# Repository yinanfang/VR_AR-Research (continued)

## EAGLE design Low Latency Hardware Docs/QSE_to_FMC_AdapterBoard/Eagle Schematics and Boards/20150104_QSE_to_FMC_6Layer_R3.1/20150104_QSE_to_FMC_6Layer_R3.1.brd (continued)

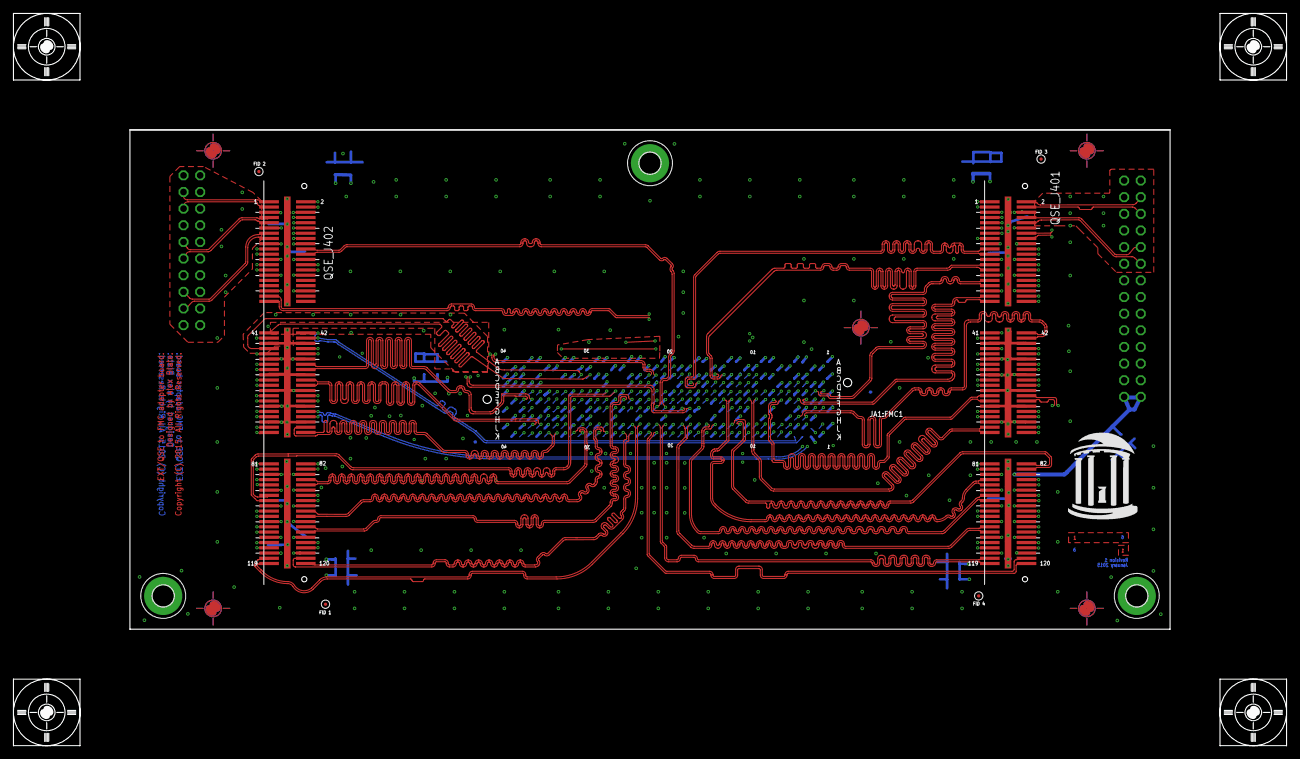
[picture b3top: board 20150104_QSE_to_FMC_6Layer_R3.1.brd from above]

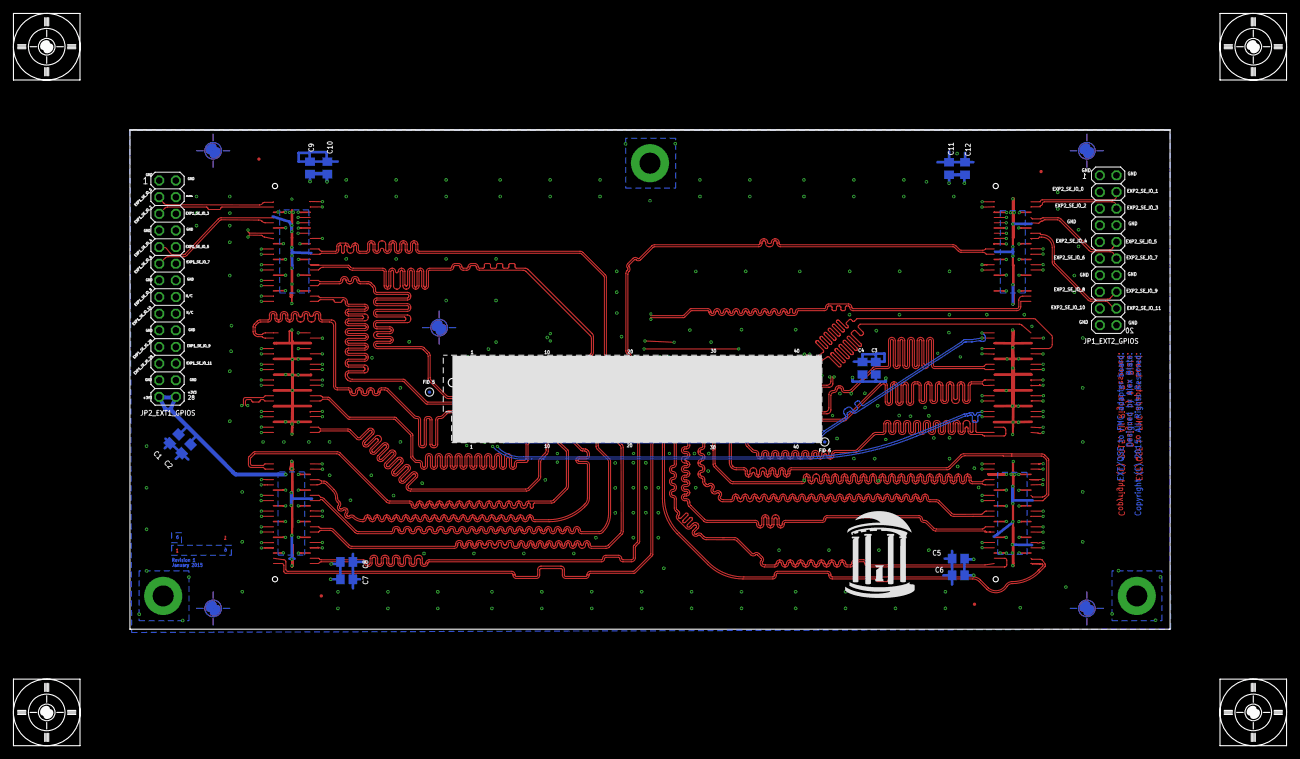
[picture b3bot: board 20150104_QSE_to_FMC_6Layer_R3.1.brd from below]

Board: 6 copper layers, 158.8 x 76.2 mm, 30 parts (15 on the bottom side), 165 nets.

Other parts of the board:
DRILEGEND: DRILEGEND
JA1:FMC1: >NAME; ASP-134486-01
QSE_J401, QSE_J402: QSE-060-01
U$2, U$3, U$4, U$5, U$6: PASS-ROUND
U$8, U$9, U$10, U$11: ALIGNMENT

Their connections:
+2V5: QSE_J401.5, QSE_J401.6, QSE_J401.11, QSE_J401.12, QSE_J401.17, QSE_J401.18, QSE_J401.23, QSE_J401.24, QSE_J401.29, QSE_J401.30, QSE_J401.35, QSE_J401.36, QSE_J402.5, QSE_J402.6, QSE_J402.11, QSE_J402.12, QSE_J402.17, QSE_J402.18, QSE_J402.23, QSE_J402.24, QSE_J402.29, QSE_J402.30, QSE_J402.35, QSE_J402.36; also elsewhere on the board
+3V3: JA1:FMC1.C39, JA1:FMC1.D36, JA1:FMC1.D38, JA1:FMC1.D40, QSE_J401.85, QSE_J401.86, QSE_J401.91, QSE_J401.92, QSE_J401.97, QSE_J401.98, QSE_J401.103, QSE_J401.104, QSE_J401.109, QSE_J401.110, QSE_J401.115, QSE_J401.116, QSE_J402.85, QSE_J402.86, QSE_J402.91, QSE_J402.92, QSE_J402.97, QSE_J402.98, QSE_J402.103, QSE_J402.104, QSE_J402.109, QSE_J402.110, QSE_J402.115, QSE_J402.116; also elsewhere on the board
CLK0_M2C_N: JA1:FMC1.H5, QSE_J401.44
CLK0_M2C_P: JA1:FMC1.H4, QSE_J401.42
CLK1_M2C_N: JA1:FMC1.G3, QSE_J401.74
CLK1_M2C_P: JA1:FMC1.G2, QSE_J401.72
CLK2_M2C_N: JA1:FMC1.K5, QSE_J402.44
CLK2_M2C_P: JA1:FMC1.K4, QSE_J402.42
CLK3_M2C_N: JA1:FMC1.J3, QSE_J402.74
CLK3_M2C_P: JA1:FMC1.J2, QSE_J402.72
EXP1_SE_CLK_IN: JA1:FMC1.H35, QSE_J401.43
EXP1_SE_CLK_OUT: JA1:FMC1.G34, QSE_J401.49
EXP1_SE_IO_0: QSE_J401.2; also elsewhere on the board
EXP1_SE_IO_1: QSE_J401.1; also elsewhere on the board
EXP1_SE_IO_2: QSE_J401.4; also elsewhere on the board
EXP1_SE_IO_3: QSE_J401.3; also elsewhere on the board
EXP1_SE_IO_4: QSE_J401.8; also elsewhere on the board
EXP1_SE_IO_5: QSE_J401.7; also elsewhere on the board
EXP1_SE_IO_6: QSE_J401.10; also elsewhere on the board
EXP1_SE_IO_7: QSE_J401.9; also elsewhere on the board
EXP1_SE_IO_8: QSE_J401.14; also elsewhere on the board
EXP1_SE_IO_9: QSE_J401.13; also elsewhere on the board
EXP1_SE_IO_10: QSE_J401.16; also elsewhere on the board
EXP1_SE_IO_11: QSE_J401.15; also elsewhere on the board
EXP1_SE_IO_28: QSE_J401.41; also elsewhere on the board
EXP1_SE_IO_29: QSE_J401.47; also elsewhere on the board
EXP2_SE_CLK_IN: JA1:FMC1.G37, QSE_J402.43
EXP2_SE_CLK_OUT: JA1:FMC1.H38, QSE_J402.49
EXP2_SE_IO_0: QSE_J402.2; also elsewhere on the board
EXP2_SE_IO_1: QSE_J402.1; also elsewhere on the board
EXP2_SE_IO_2: QSE_J402.4; also elsewhere on the board
EXP2_SE_IO_3: QSE_J402.3; also elsewhere on the board
EXP2_SE_IO_4: QSE_J402.8; also elsewhere on the board
EXP2_SE_IO_5: QSE_J402.7; also elsewhere on the board
EXP2_SE_IO_6: QSE_J402.10; also elsewhere on the board
EXP2_SE_IO_7: QSE_J402.9; also elsewhere on the board
EXP2_SE_IO_8: QSE_J402.14; also elsewhere on the board
EXP2_SE_IO_9: QSE_J402.13; also elsewhere on the board
EXP2_SE_IO_10: QSE_J402.16; also elsewhere on the board
EXP2_SE_IO_11: QSE_J402.15; also elsewhere on the board
FMC_SCL: JA1:FMC1.C30, QSE_J402.41
FMC_SDA: JA1:FMC1.C31, QSE_J402.47
GBCTCLK1_N: JA1:FMC1.B21, QSE_J401.50
GBCTCLK1_P: JA1:FMC1.B20, QSE_J401.48
GBTCLK0_N: JA1:FMC1.D5, QSE_J401.61
GBTCLK0_P: JA1:FMC1.D4, QSE_J401.59
GND: JA1:FMC1.A1, JA1:FMC1.A4, JA1:FMC1.A5, JA1:FMC1.A8, JA1:FMC1.A9, JA1:FMC1.A12, JA1:FMC1.A13, JA1:FMC1.A16, JA1:FMC1.A17, JA1:FMC1.A20, JA1:FMC1.A21, JA1:FMC1.A24, JA1:FMC1.A25, JA1:FMC1.A28, JA1:FMC1.A29, JA1:FMC1.A32, JA1:FMC1.A33, JA1:FMC1.A36, JA1:FMC1.A37, JA1:FMC1.A40, JA1:FMC1.B2, JA1:FMC1.B3, JA1:FMC1.B6, JA1:FMC1.B7, JA1:FMC1.B10, JA1:FMC1.B11, JA1:FMC1.B14, JA1:FMC1.B15, JA1:FMC1.B18, JA1:FMC1.B19, JA1:FMC1.B22, JA1:FMC1.B23, JA1:FMC1.B26, JA1:FMC1.B27, JA1:FMC1.B30, JA1:FMC1.B31, JA1:FMC1.B34, JA1:FMC1.B35, JA1:FMC1.B38, JA1:FMC1.B39, JA1:FMC1.C1, JA1:FMC1.C4, JA1:FMC1.C5, JA1:FMC1.C8, JA1:FMC1.C9, JA1:FMC1.C12, JA1:FMC1.C13, JA1:FMC1.C16, JA1:FMC1.C17, JA1:FMC1.C20, JA1:FMC1.C21, JA1:FMC1.C24, JA1:FMC1.C25, JA1:FMC1.C28, JA1:FMC1.C29, JA1:FMC1.C32, JA1:FMC1.C33, JA1:FMC1.C36, JA1:FMC1.C38, JA1:FMC1.C40, JA1:FMC1.D2, JA1:FMC1.D3, JA1:FMC1.D6, JA1:FMC1.D7, JA1:FMC1.D10, JA1:FMC1.D13, JA1:FMC1.D16, JA1:FMC1.D19, JA1:FMC1.D22, JA1:FMC1.D25, JA1:FMC1.D28, JA1:FMC1.D37, JA1:FMC1.D39, JA1:FMC1.E1, JA1:FMC1.E4, JA1:FMC1.E5, JA1:FMC1.E8, JA1:FMC1.E11, JA1:FMC1.E14, JA1:FMC1.E17, JA1:FMC1.E20, JA1:FMC1.E23, JA1:FMC1.E26, JA1:FMC1.E29, JA1:FMC1.E32, JA1:FMC1.E35, JA1:FMC1.E38, JA1:FMC1.E40, JA1:FMC1.F2, JA1:FMC1.F3, JA1:FMC1.F6, JA1:FMC1.F9, JA1:FMC1.F12, JA1:FMC1.F15, JA1:FMC1.F18, JA1:FMC1.F21, JA1:FMC1.F24, JA1:FMC1.F27, JA1:FMC1.F30, JA1:FMC1.F33, JA1:FMC1.F36, JA1:FMC1.F39, JA1:FMC1.G1, JA1:FMC1.G4, JA1:FMC1.G5, JA1:FMC1.G8, JA1:FMC1.G11, JA1:FMC1.G14, JA1:FMC1.G17, JA1:FMC1.G20, JA1:FMC1.G23, JA1:FMC1.G26, JA1:FMC1.G29, JA1:FMC1.G30, JA1:FMC1.G32, JA1:FMC1.G33, JA1:FMC1.G35, JA1:FMC1.G36, JA1:FMC1.G38, JA1:FMC1.G40, JA1:FMC1.H3, JA1:FMC1.H6, JA1:FMC1.H9, JA1:FMC1.H12, JA1:FMC1.H15, JA1:FMC1.H18, JA1:FMC1.H21, JA1:FMC1.H24, JA1:FMC1.H27, JA1:FMC1.H30, JA1:FMC1.H31, JA1:FMC1.H33, JA1:FMC1.H34, JA1:FMC1.H36, JA1:FMC1.H37, JA1:FMC1.H39, JA1:FMC1.J1, JA1:FMC1.J4, JA1:FMC1.J5, JA1:FMC1.J8, JA1:FMC1.J11, JA1:FMC1.J14, JA1:FMC1.J17, JA1:FMC1.J20, JA1:FMC1.J23, JA1:FMC1.J26, JA1:FMC1.J29, JA1:FMC1.J32, JA1:FMC1.J35, JA1:FMC1.J38, JA1:FMC1.J40, JA1:FMC1.K2, JA1:FMC1.K3, JA1:FMC1.K6, JA1:FMC1.K9, JA1:FMC1.K12, JA1:FMC1.K15, JA1:FMC1.K18, JA1:FMC1.K21, JA1:FMC1.K24, JA1:FMC1.K27, JA1:FMC1.K30, JA1:FMC1.K33, JA1:FMC1.K36, JA1:FMC1.K39, QSE_J401.45, QSE_J401.46, QSE_J401.51, QSE_J401.52, QSE_J401.57, QSE_J401.58, QSE_J401.63, QSE_J401.64, QSE_J401.69, QSE_J401.70, QSE_J401.75, QSE_J401.76, QSE_J401.GND1, QSE_J401.GND2, QSE_J401.GND3, QSE_J401.GND4, QSE_J401.GND5, QSE_J401.GND6, QSE_J401.GND7, QSE_J401.GND8, QSE_J401.GND9, QSE_J401.GND10, QSE_J401.GND11, QSE_J401.GND12, QSE_J402.45, QSE_J402.46, QSE_J402.51, QSE_J402.52, QSE_J402.57, QSE_J402.58, QSE_J402.63, QSE_J402.64, QSE_J402.69, QSE_J402.70, QSE_J402.75, QSE_J402.76, QSE_J402.GND1, QSE_J402.GND2, QSE_J402.GND3, QSE_J402.GND4, QSE_J402.GND5, QSE_J402.GND6, QSE_J402.GND7, QSE_J402.GND8, QSE_J402.GND9, QSE_J402.GND10, QSE_J402.GND11, QSE_J402.GND12; also elsewhere on the board
HDP0_N: JA1:FMC1.F5, QSE_J401.39
HDP0_P: JA1:FMC1.F4, QSE_J401.37
HDP1_N: JA1:FMC1.E3, QSE_J401.33
HDP1_P: JA1:FMC1.E2, QSE_J401.31
HDP2_N: JA1:FMC1.K8, QSE_J401.55
HDP2_P: JA1:FMC1.K7, QSE_J401.53
HDP3_N: JA1:FMC1.J7, QSE_J401.56
HDP3_P: JA1:FMC1.J6, QSE_J401.54
HDP4_N: JA1:FMC1.F8, QSE_J401.67
HDP4_P: JA1:FMC1.F7, QSE_J401.65
HDP5_N: JA1:FMC1.E7, QSE_J401.62
HDP5_P: JA1:FMC1.E6, QSE_J401.60
HDP6_N: JA1:FMC1.K11, QSE_J401.73
HDP6_P: JA1:FMC1.K10, QSE_J401.71
HDP7_N: JA1:FMC1.J10, QSE_J401.68
HDP7_P: JA1:FMC1.J9, QSE_J401.66
HDP8_N: JA1:FMC1.F11, QSE_J401.79
HDP8_P: JA1:FMC1.F10, QSE_J401.77
HDP9_N: JA1:FMC1.E10, QSE_J401.80
HDP9_P: JA1:FMC1.E9, QSE_J401.78
HDP10_N: JA1:FMC1.K14, QSE_J401.83
HDP10_P: JA1:FMC1.K13, QSE_J401.81
HDP11_N: JA1:FMC1.J13, QSE_J401.84
HDP11_P: JA1:FMC1.J12, QSE_J401.82
HDP12_N: JA1:FMC1.F14, QSE_J401.89
HDP12_P: JA1:FMC1.F13, QSE_J401.87
HDP13_N: JA1:FMC1.E13, QSE_J401.90
HDP13_P: JA1:FMC1.E12, QSE_J401.88
HDP14_N: JA1:FMC1.J16, QSE_J401.95
HDP14_P: JA1:FMC1.J15, QSE_J401.93
HDP15_N: JA1:FMC1.F17, QSE_J401.96
HDP15_P: JA1:FMC1.F16, QSE_J401.94
HDP16_N: JA1:FMC1.E16, QSE_J401.101
HDP16_P: JA1:FMC1.E15, QSE_J401.99
HDP17_N: JA1:FMC1.K17, QSE_J401.102
HDP17_P: JA1:FMC1.K16, QSE_J401.100
HDP18_N: JA1:FMC1.J19, QSE_J401.107
HDP18_P: JA1:FMC1.J18, QSE_J401.105
HDP19_N: JA1:FMC1.F20, QSE_J401.108
HDP19_P: JA1:FMC1.F19, QSE_J401.106
HDP20_N: JA1:FMC1.E19, QSE_J401.113
HDP20_P: JA1:FMC1.E18, QSE_J401.111
HDP21_N: JA1:FMC1.K20, QSE_J401.114
HDP21_P: JA1:FMC1.K19, QSE_J401.112
HDP22_N: JA1:FMC1.J22, QSE_J401.119
HDP22_P: JA1:FMC1.J21, QSE_J401.117
HDP23_N: JA1:FMC1.K23, QSE_J401.120
HDP23_P: JA1:FMC1.K22, QSE_J401.118
HDQ0_N: JA1:FMC1.K26, QSE_J402.120
HDQ0_P: JA1:FMC1.K25, QSE_J402.118
HDQ1_N: JA1:FMC1.J25, QSE_J402.119
HDQ1_P: JA1:FMC1.J24, QSE_J402.117
HDQ2_N: JA1:FMC1.F23, QSE_J402.114
HDQ2_P: JA1:FMC1.F22, QSE_J402.112
HDQ3_N: JA1:FMC1.E22, QSE_J402.113
HDQ3_P: JA1:FMC1.E21, QSE_J402.111
HDQ4_N: JA1:FMC1.F26, QSE_J402.108
HDQ4_P: JA1:FMC1.F25, QSE_J402.106
HDQ5_N: JA1:FMC1.E25, QSE_J402.107
HDQ5_P: JA1:FMC1.E24, QSE_J402.105
HDQ6_N: JA1:FMC1.K29, QSE_J402.102
HDQ6_P: JA1:FMC1.K28, QSE_J402.100
HDQ7_N: JA1:FMC1.J28, QSE_J402.101
HDQ7_P: JA1:FMC1.J27, QSE_J402.99
HDQ8_N: JA1:FMC1.F29, QSE_J402.96
HDQ8_P: JA1:FMC1.F28, QSE_J402.94
HDQ9_N: JA1:FMC1.E28, QSE_J402.95
HDQ9_P: JA1:FMC1.E27, QSE_J402.93
HDQ10_N: JA1:FMC1.K32, QSE_J402.90
HDQ10_P: JA1:FMC1.K31, QSE_J402.88
HDQ11_N: JA1:FMC1.J31, QSE_J402.89
HDQ11_P: JA1:FMC1.J30, QSE_J402.87
HDQ12_N: JA1:FMC1.F32, QSE_J402.84
HDQ12_P: JA1:FMC1.F31, QSE_J402.82
HDQ13_N: JA1:FMC1.E31, QSE_J402.83
HDQ13_P: JA1:FMC1.E30, QSE_J402.81
HDQ14_N: JA1:FMC1.K35, QSE_J402.80
HDQ14_P: JA1:FMC1.K34, QSE_J402.78
HDQ15_N: JA1:FMC1.J34, QSE_J402.79
HDQ15_P: JA1:FMC1.J33, QSE_J402.77
HDQ16_N: JA1:FMC1.F35, QSE_J402.68
HDQ16_P: JA1:FMC1.F34, QSE_J402.66
HDQ17_N: JA1:FMC1.K38, QSE_J402.73
HDQ17_P: JA1:FMC1.K37, QSE_J402.71
HDQ18_N: JA1:FMC1.J37, QSE_J402.62
HDQ18_P: JA1:FMC1.J36, QSE_J402.60
HDQ19_N: JA1:FMC1.E34, QSE_J402.67
HDQ19_P: JA1:FMC1.E33, QSE_J402.65
HDQ20_N: JA1:FMC1.F38, QSE_J402.56
HDQ20_P: JA1:FMC1.F37, QSE_J402.54
HDQ21_N: JA1:FMC1.E37, QSE_J402.55
HDQ21_P: JA1:FMC1.E36, QSE_J402.53
LA05_N: JA1:FMC1.D12, QSE_J401.34
LA05_P: JA1:FMC1.D11, QSE_J401.32
LA06_N: JA1:FMC1.C11, QSE_J401.40
LA06_P: JA1:FMC1.C10, QSE_J401.38
LA08_N: JA1:FMC1.G13, QSE_J401.28
LA08_P: JA1:FMC1.G12, QSE_J401.26
LA09_N: JA1:FMC1.D15, QSE_J401.22
LA09_P: JA1:FMC1.D14, QSE_J401.20
LA10_N: JA1:FMC1.C15, QSE_J401.27
LA10_P: JA1:FMC1.C14, QSE_J401.25
LA13_N: JA1:FMC1.D18, QSE_J401.21
LA13_P: JA1:FMC1.D17, QSE_J401.19
LA14_N: JA1:FMC1.C19, QSE_J402.39
LA14_P: JA1:FMC1.C18, QSE_J402.37
LA16_N: JA1:FMC1.G19, QSE_J402.61
LA16_P: JA1:FMC1.G18, QSE_J402.59
LA18_N: JA1:FMC1.C23, QSE_J402.50
LA18_P: JA1:FMC1.C22, QSE_J402.48
LA20_N: JA1:FMC1.G22, QSE_J402.22
LA20_P: JA1:FMC1.G21, QSE_J402.20
LA22_N: JA1:FMC1.G25, QSE_J402.28
LA22_P: JA1:FMC1.G24, QSE_J402.26
LA23_N: JA1:FMC1.D24, QSE_J402.21
LA23_P: JA1:FMC1.D23, QSE_J402.19
LA25_N: JA1:FMC1.G28, QSE_J402.27
LA25_P: JA1:FMC1.G27, QSE_J402.25

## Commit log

2015-08-14 Backup VR_AR research
